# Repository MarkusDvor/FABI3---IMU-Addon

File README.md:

# FABI3---IMU-Addon
The FABI3 has the possibility to connect addon boards via the integrated RJ-25 connector.
Goal of this project is to develop an addon with an IMU, to have the possibility to trigger different functions based on accelerometer or gyroscope data.

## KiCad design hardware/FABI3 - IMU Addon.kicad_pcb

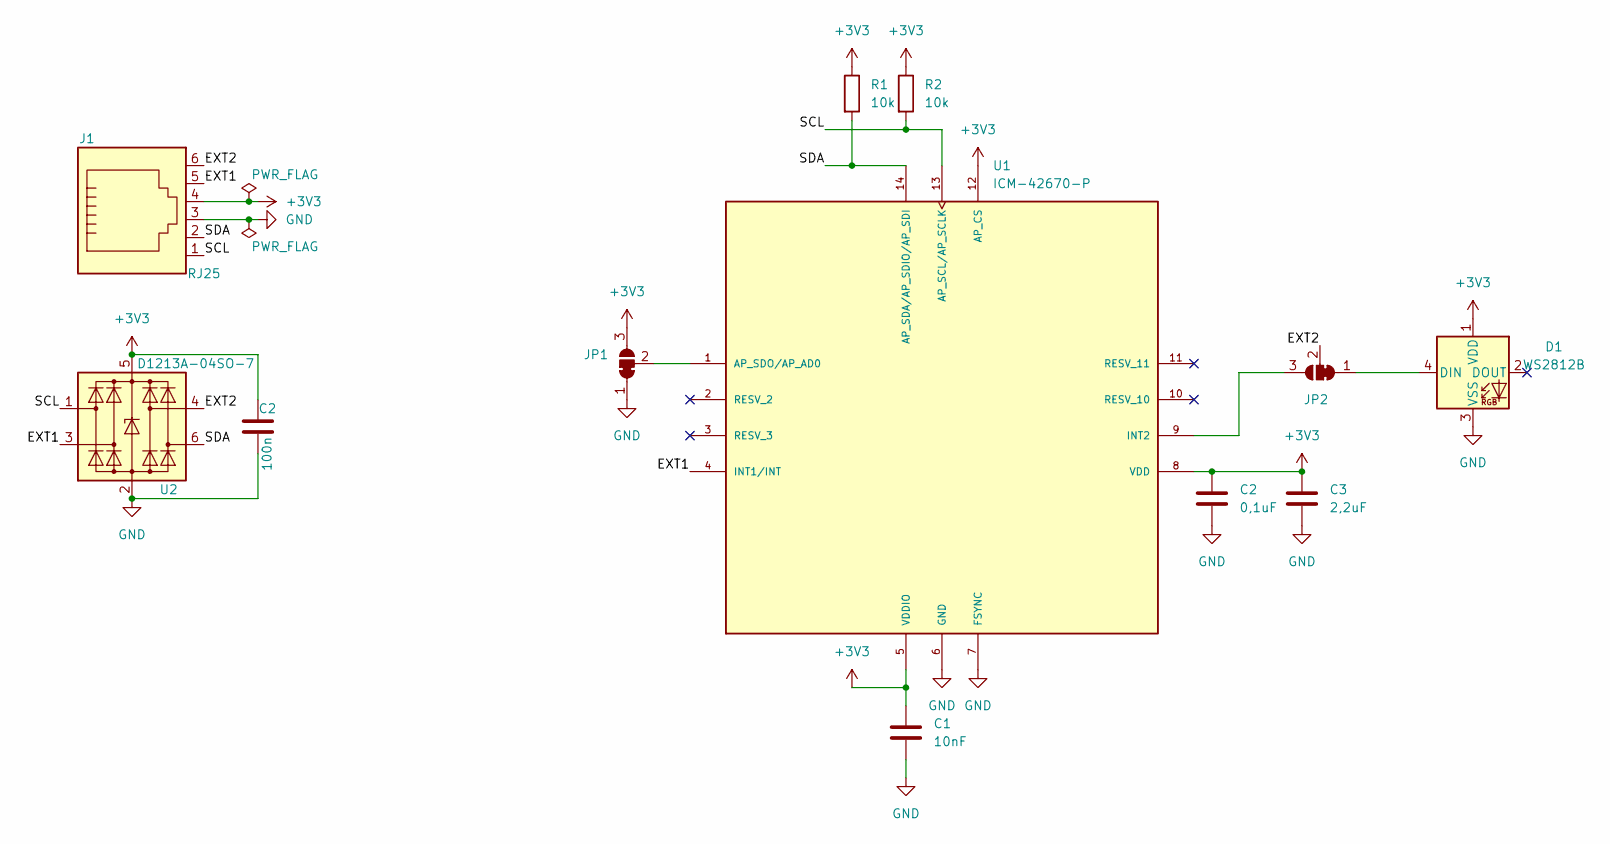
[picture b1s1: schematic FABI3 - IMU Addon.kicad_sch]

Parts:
C1: 10nF; C_0603_1608Metric_Pad1.08x0.95mm_HandSolder; DigiKey 399-C0603C103K9RAC7867CT-ND
C2: 0,1uF; C_0603_1608Metric_Pad1.08x0.95mm_HandSolder; DigiKey 478-KGM15AR70J104KMCT-ND
C3: 2,2uF; C_0603_1608Metric_Pad1.08x0.95mm_HandSolder; DigiKey 311-1795-1-ND - Gurtabschnitt
D1: WS2812B; LED_WS2812B_PLCC4_5.0x5.0mm_P3.2mm
J1: RJ25; RJ12_Amphenol_54601; DigiKey 609-4729-ND
JP1, JP2: SolderJumper_3_Bridged12; SolderJumper-3_P1.3mm_Bridged12_RoundedPad1.0x1.5mm_NumberL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
R1, R2: 10k; R_0603_1608Metric_Pad0.98x0.95mm_HandSolder; DigiKey 2019-RN73R1JTTD1002F100CT-ND
U1: ICM-42670-P; IC_ICM-42670-P; DigiKey 1428-ICM-42670-PCT-ND
U2: D1213A-04SO-7; SC-74-6_1.5x2.9mm_P0.95mm; Digikey D1213A-04SO-7DICT-ND

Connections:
+3V3: C1.1, C2.1, C3.1, D1.1 (VDD), J1.4, JP1.3 (B), R1.1, R2.1, U1.5 (VDDIO), U1.8 (VDD), U1.12 (AP_CS), U2.5 (VBUS); also elsewhere on the board
/EXT1: J1.5, U1.4 (INT1/INT), U2.3 (I/O2)
/EXT2: J1.6, JP2.2 (C), U2.4 (I/O3)
/SCL: J1.1, R2.2, U1.13 (AP_SCL/AP_SCLK), U2.1 (I/O1)
/SDA: J1.2, R1.2, U1.14 (AP_SDA/AP_SDIO/AP_SDI), U2.6 (I/O4)
GND: C1.2, C2.2, C3.2, D1.3 (VSS), J1.3, JP1.1 (A), U1.6 (GND), U1.7 (FSYNC), U2.2 (GND); also elsewhere on the board
unnamed: D1.4 (DIN), JP2.1 (A)
unnamed: JP1.2 (C), U1.1 (AP_SDO/AP_AD0)
unnamed: JP2.3 (B), U1.9 (INT2)

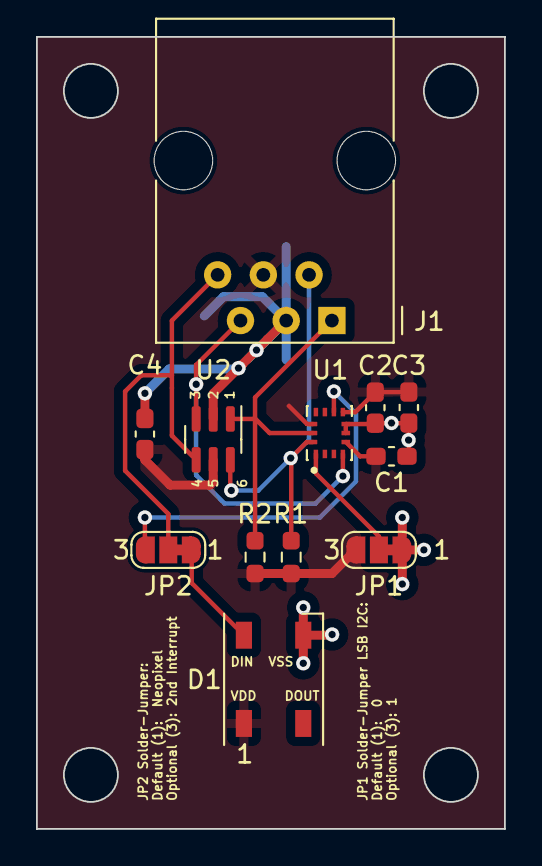
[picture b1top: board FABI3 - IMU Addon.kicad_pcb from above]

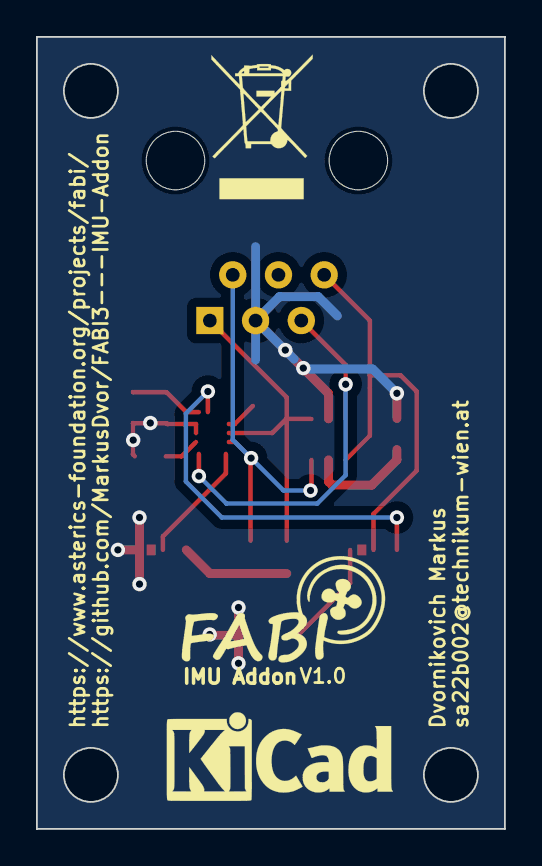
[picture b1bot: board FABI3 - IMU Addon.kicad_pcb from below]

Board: 2 copper layers, 26.0 x 44.0 mm, 15 parts (3 on the bottom side), 9 nets.

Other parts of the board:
C4: 100n; C_0603_1608Metric_Pad1.08x0.95mm_HandSolder
LOGO1: Logo_FABI; FABI_Logo_s
LOGO2: Logo_KiCAD; KiCad-Logo_5mm_SilkScreen
LOGO4: Logo_WEEE; WEEE-Logo_5.6x8mm_SilkScreen

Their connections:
+3V3: C4.1; also elsewhere on the board
GND: C4.2; also elsewhere on the board

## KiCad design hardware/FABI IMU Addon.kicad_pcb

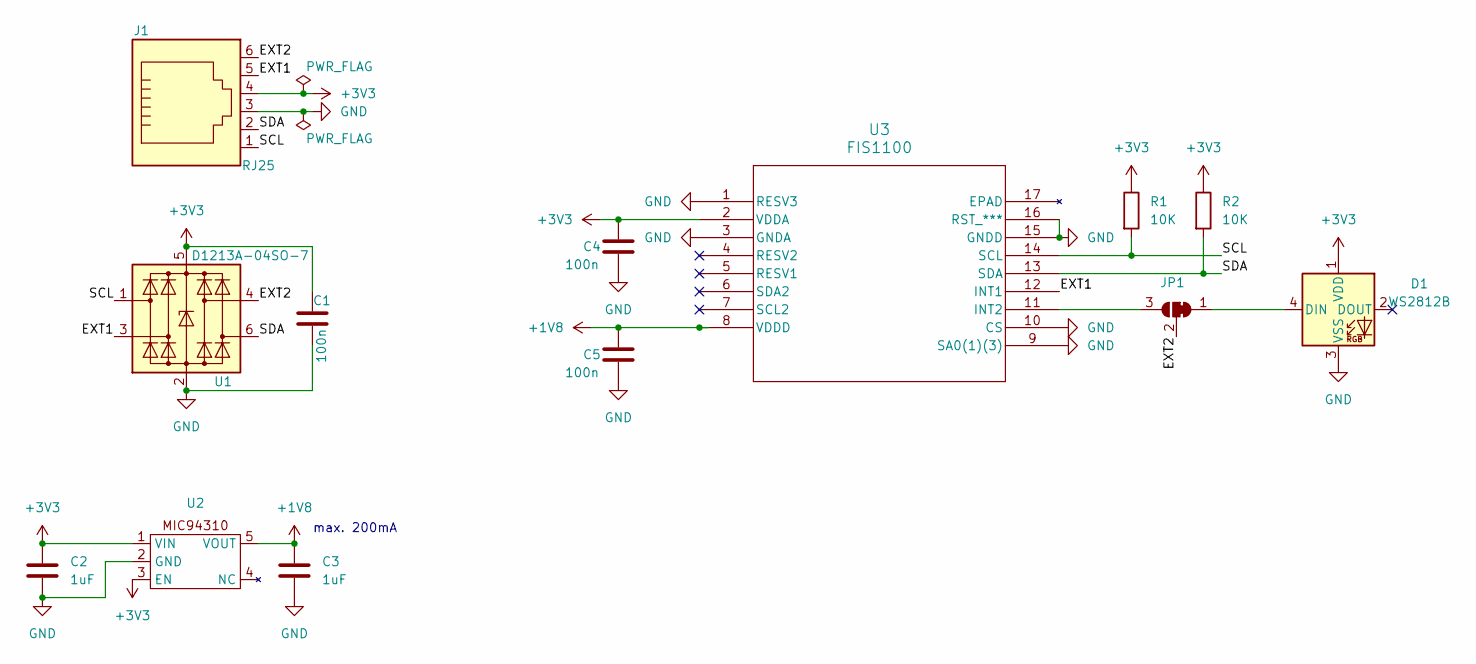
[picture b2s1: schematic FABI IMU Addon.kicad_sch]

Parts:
C1, C4, C5: 100n; C_0603_1608Metric_Pad1.08x0.95mm_HandSolder; Digikey 1276-CL10B104KB8NNNLCT-ND
C2, C3: 1uF; C_0603_1608Metric_Pad1.08x0.95mm_HandSolder; DigiKey 1276-1036-1-ND
D1: WS2812B; LED_WS2812B_PLCC4_5.0x5.0mm_P3.2mm
J1: RJ25; RJ12_Amphenol_54601; DigiKey 609-4729-ND
JP1: SolderJumper_3_Bridged12; SolderJumper-3_P1.3mm_Bridged12_RoundedPad1.0x1.5mm_NumberL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
R1: 10K; R_0603_1608Metric_Pad0.98x0.95mm_HandSolder; Digikey 2019-RN73R1JTTD1002F100CT-ND
R2: 10K; R_0603_1608Metric_Pad0.98x0.95mm_HandSolder; DigiKey 2019-RN73R1JTTD1002F100CT-ND
U1: D1213A-04SO-7; SC-74-6_1.5x2.9mm_P0.95mm; Digikey D1213A-04SO-7DICT-ND
U2: MIC94310; SOT-23-5_HandSoldering; DigiKey 576-4769-1-ND
U3: FIS1100; LGA16_FIS1100_ONS; Digikey 2156-FIS1100-ND

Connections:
+1V8: C3.1, C5.1, U2.5 (VOUT), U3.8 (VDDD)
+3V3: C1.1, C2.1, C4.1, D1.1 (VDD), J1.4, R1.1, R2.1, U1.5 (VBUS), U2.1 (VIN), U2.3 (EN), U3.2 (VDDA)
/EXT1: J1.5, U1.3 (I/O2), U3.12 (INT1)
/EXT2: J1.6, JP1.2 (C), U1.4 (I/O3)
/SCL: J1.1, R1.2, U1.1 (I/O1), U3.14 (SCL)
/SDA: J1.2, R2.2, U1.6 (I/O4), U3.13 (SDA)
GND: C1.2, C2.2, C3.2, C4.2, C5.2, D1.3 (VSS), J1.3, U1.2 (GND), U2.2 (GND), U3.1 (RESV3), U3.3 (GNDA), U3.9 (SA0(1)(3)), U3.10 (CS), U3.15 (GNDD), U3.16 (RST_***)
unnamed: D1.4 (DIN), JP1.1 (A)
unnamed: JP1.3 (B), U3.11 (INT2)

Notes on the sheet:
max. 200mA

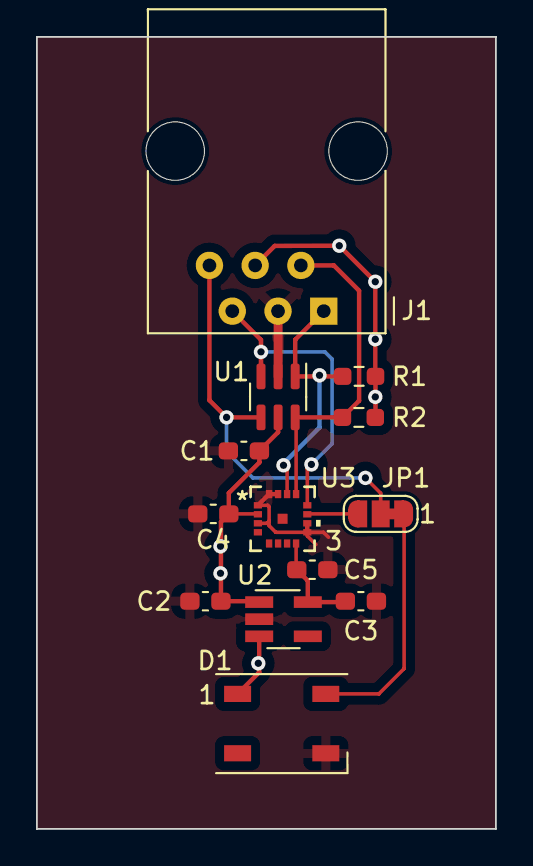
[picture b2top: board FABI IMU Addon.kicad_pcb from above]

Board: 2 copper layers, 25.5 x 44.0 mm, 13 parts (0 on the bottom side), 9 nets.

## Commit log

2023-10-20 Added KiCad
2023-10-20 Added Hardware
2023-10-20 Added CSV-File
2023-10-20 Added Datasheets
2023-11-15 Added hardware back in after deletion
    Changes made to the PCB to change to a 3V3 solution instead of going for a 1V8 solution.
2024-01-07 Added new hardware back in
2024-01-07 Added Testcode
2024-01-07 Added FabiWare
